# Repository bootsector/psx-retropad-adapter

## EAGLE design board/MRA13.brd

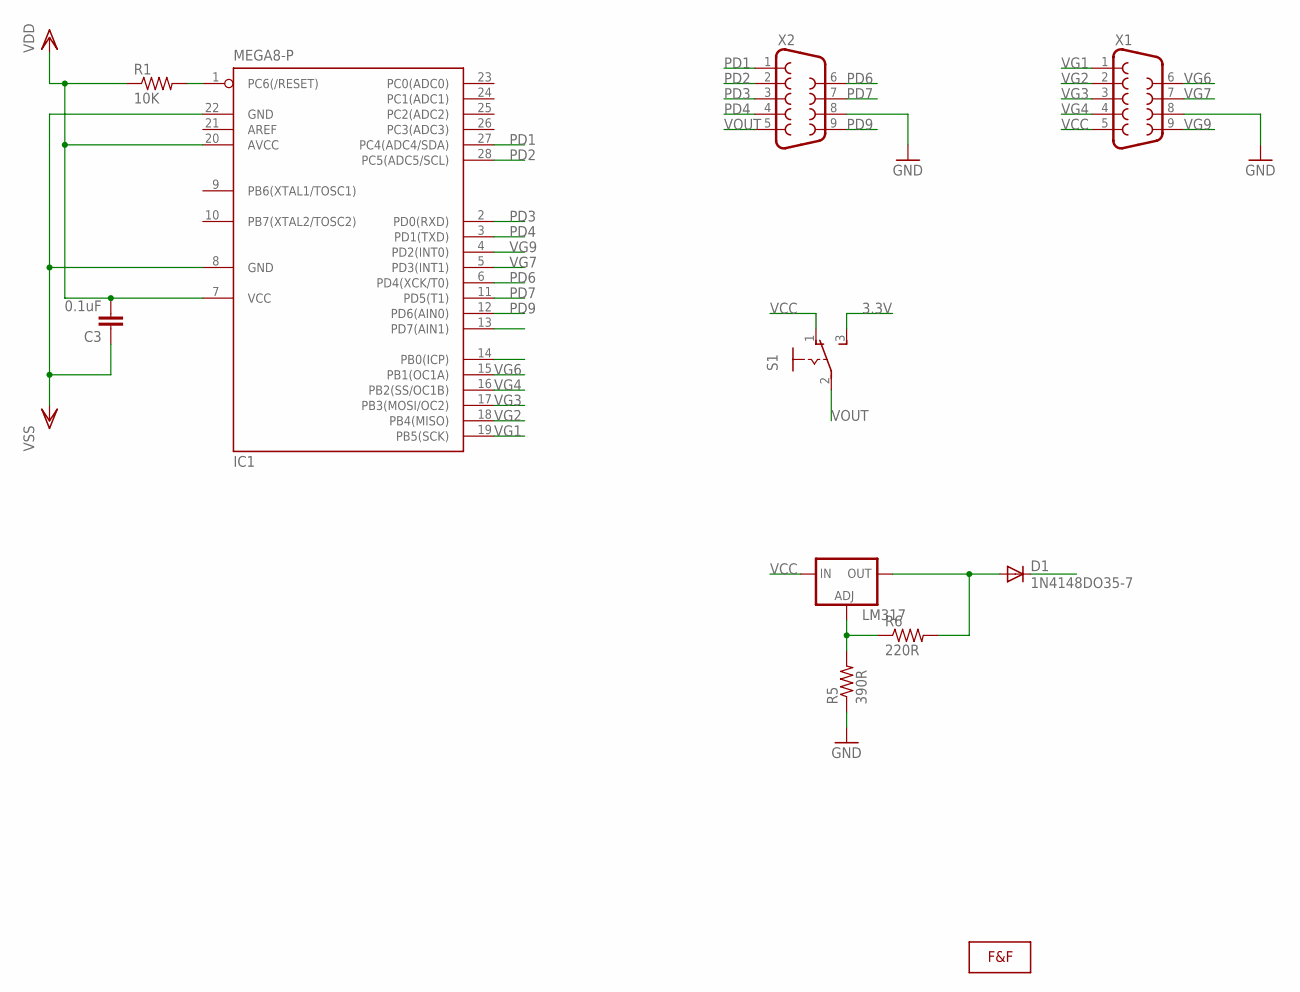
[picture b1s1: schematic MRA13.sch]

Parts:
C3: 0.1uF; C050-024X044
D1: 1N4148DO35-7; DO35-7
IC1: MEGA8-P; DIL28-3
LM317: LM317TS; 317TS
R1: 10K; 0207/10
R5: 390R; 0207/10
R6: 220R; 0207/10
S1: CHAVE
U$1: LOGOLOGO_WITHOUT_SMOKE_SMALL; LOGO2_SMALL
X1, X2: DB9MALE; DB9_MALE

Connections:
3.3V: D1.C, S1.3 (S)
GND: C3.1, IC1.8 (GND), IC1.22 (GND), R5.1, X1.8, X2.8
unnamed: IC1.1 (PC6(/RESET)), R1.2
unnamed: D1.A, LM317.2 (OUT), R6.2
unnamed: LM317.1 (ADJ), R5.2, R6.1
PD1: IC1.27 (PC4(ADC4/SDA)), X2.1
PD2: IC1.28 (PC5(ADC5/SCL)), X2.2
PD3: IC1.2 (PD0(RXD)), X2.3
PD4: IC1.3 (PD1(TXD)), X2.4
PD6: IC1.6 (PD4(XCK/T0)), X2.6
PD7: IC1.11 (PD5(T1)), X2.7
PD9: IC1.12 (PD6(AIN0)), X2.9
VCC: LM317.3 (IN), S1.1 (O), X1.5
VG1: IC1.19 (PB5(SCK)), X1.1
VG2: IC1.18 (PB4(MISO)), X1.2
VG3: IC1.17 (PB3(MOSI/OC2)), X1.3
VG4: IC1.16 (PB2(SS/OC1B)), X1.4
VG6: IC1.15 (PB1(OC1A)), X1.6
VG7: IC1.5 (PD3(INT1)), X1.7
VG9: IC1.4 (PD2(INT0)), X1.9
VOUT: C3.2, IC1.7 (VCC), IC1.20 (AVCC), R1.1, S1.2, X2.5

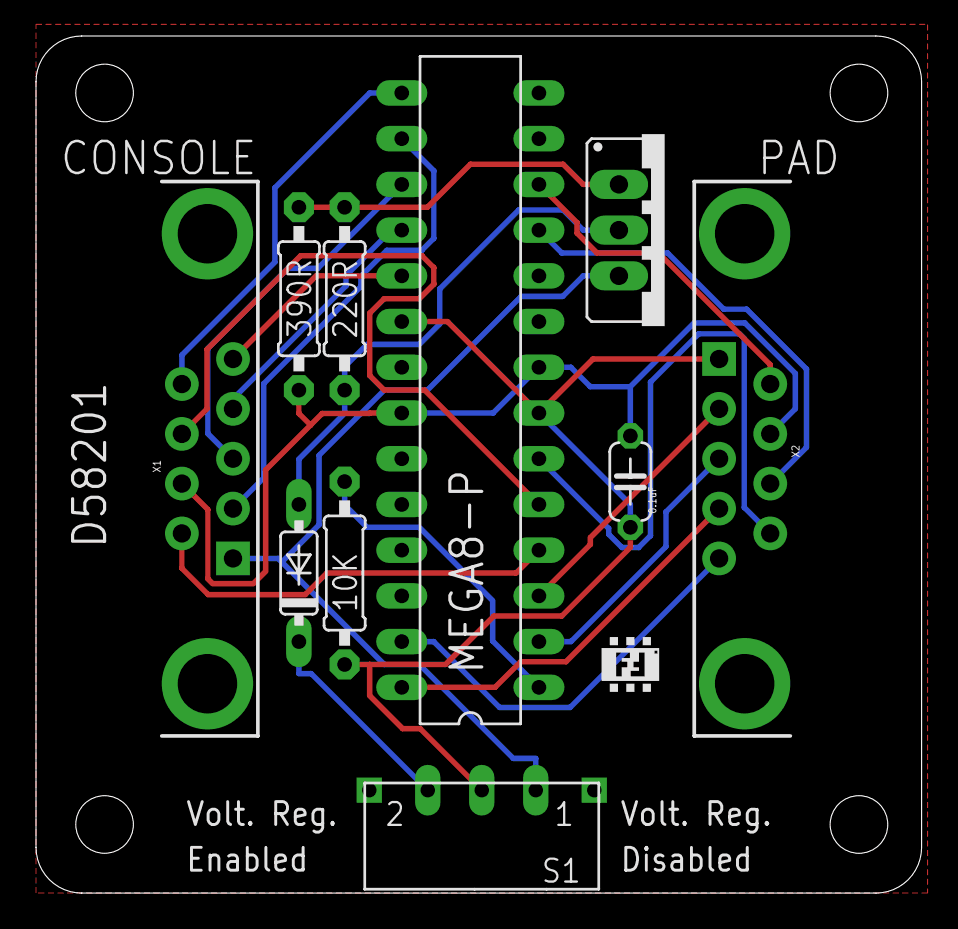
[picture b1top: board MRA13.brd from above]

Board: 2 copper layers, 49.2 x 47.6 mm, 11 parts (0 on the bottom side), 21 nets.

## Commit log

2012-09-07 Initial Commit.
2012-09-23 Added support for atmega168p. Now using calibration data from CC for analog sticks thresholds.
2012-09-23 Reading calibration data with two reads now (works with the WRA).
2012-09-30 Fixed Sega Genesis controller driver so it works fine with Sega Master System, Atari 2600 and compatibles.
2013-01-26 - Changed firmware so it's compatible with new board revision (1.2) - Added support to GC and N64 controllers! :D
2013-01-26 Added board/schematics files and asm version of the GC/N64 pad driver
2014-08-14 Improved PSPadEmu. Tests pending...
2014-08-14 Board revision 1.3
2014-08-15 Confirmed working with PSX-X360 converter (the one which doesnt need an USB X360 controller attached)
2014-08-16 PSPadEmu code cleanup
2014-08-21 PSPadEmu bugfix
2014-08-22 More PSPadEmu tweaks
2014-08-23 Disabled Timer0 overflow interrupt because we dont need it. Added support for TG16 joysticks. Updated pad detection routine based on WRA.
2014-08-24 No .DS_Store files
2014-08-24 Analog button press support added
2014-08-24 Code cleanup
2014-08-25 Home button on Wii Classic Controller now triggers Analog button push
2014-08-25 Properly implemented mode toggling mechanism
2014-08-27 Changed email address in copyright disclaimers
2015-04-02 Added support for the Wii Classic Controller Pro
2015-04-27 Detection of invalid calibration data on knock-off classic controllers
